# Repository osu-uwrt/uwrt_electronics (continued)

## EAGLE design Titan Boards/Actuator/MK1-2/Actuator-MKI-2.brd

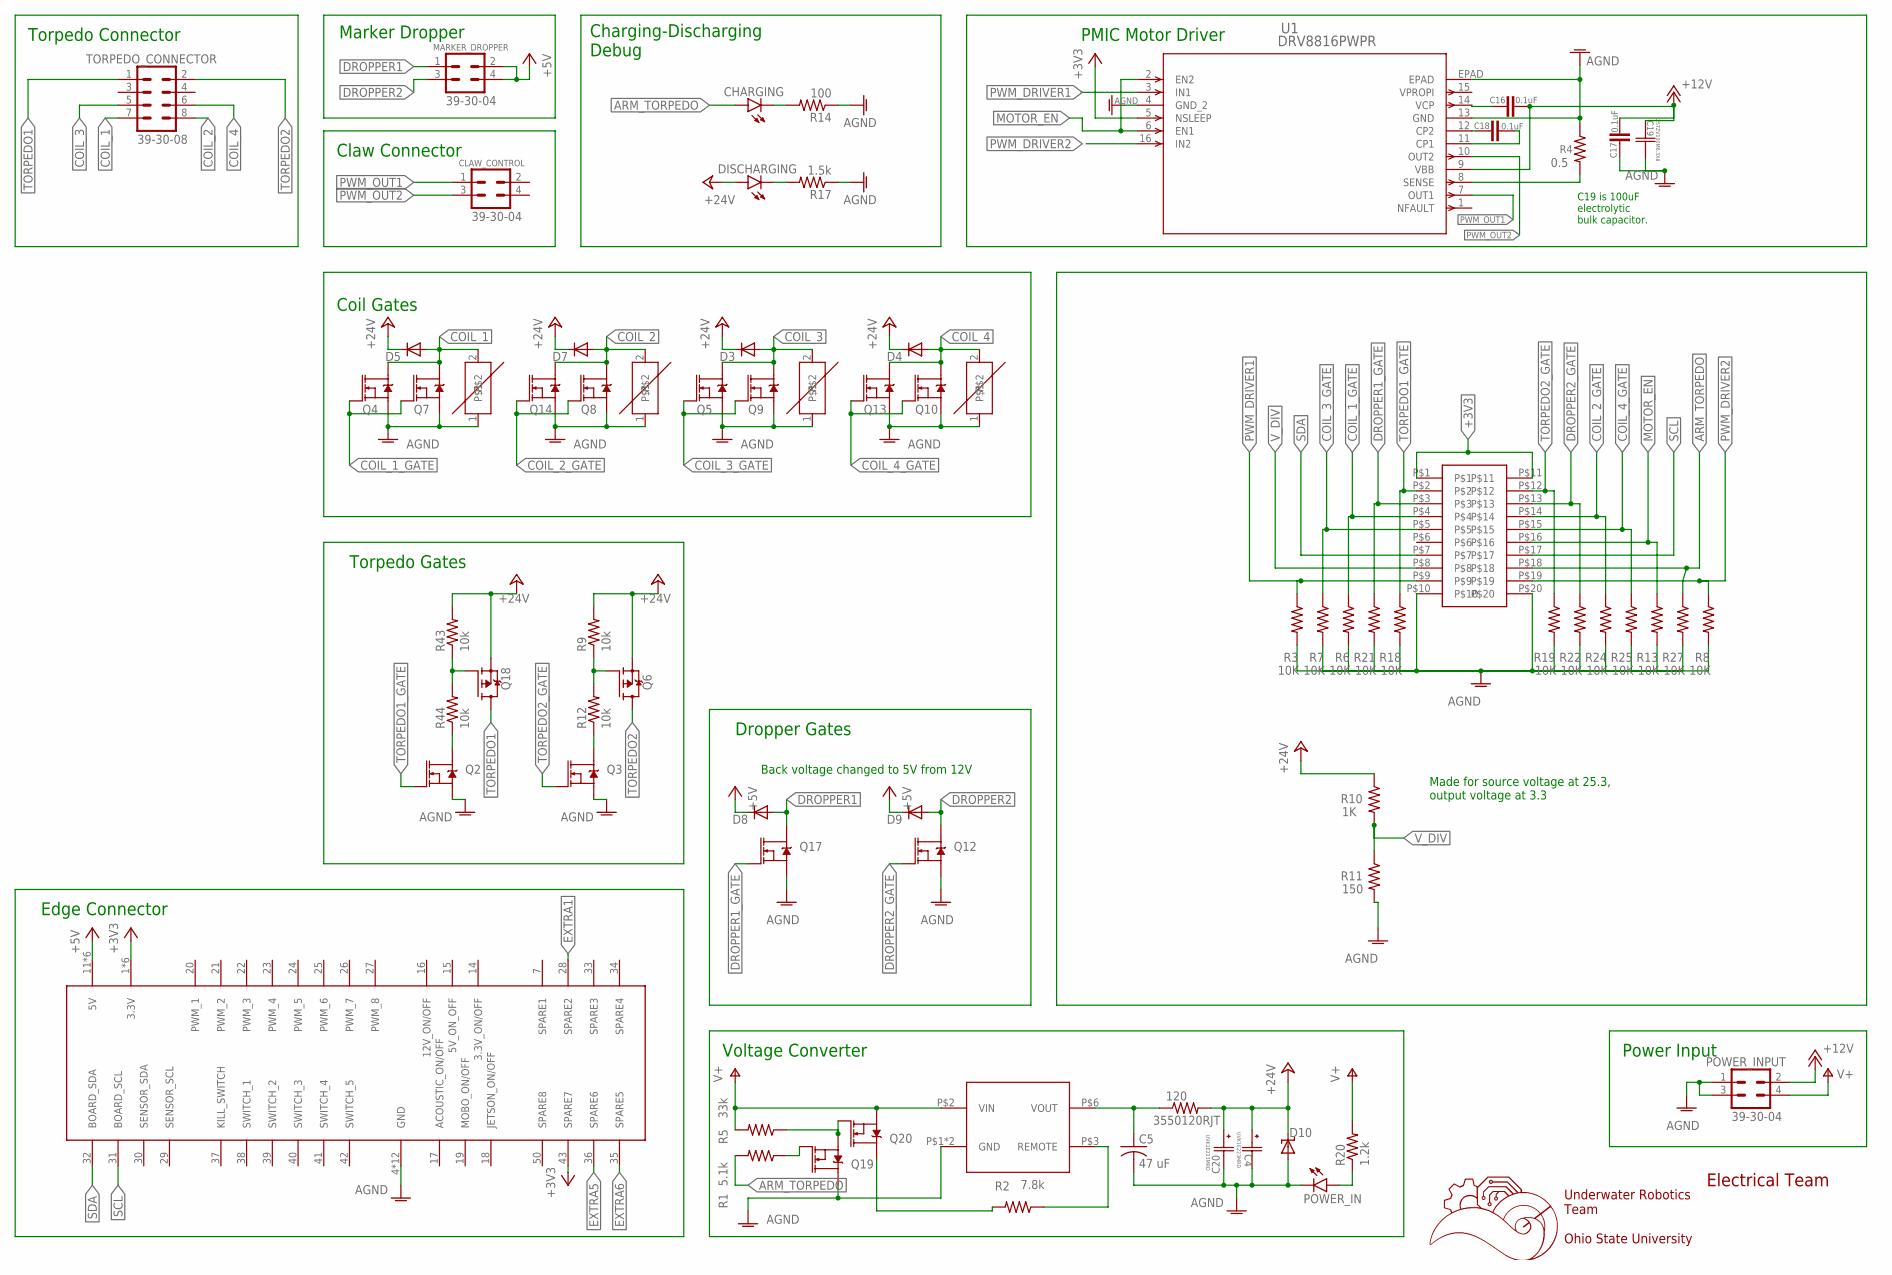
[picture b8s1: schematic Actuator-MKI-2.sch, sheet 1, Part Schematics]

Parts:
120: 3550120RJT
C4, C20: UVK1E223MRD; CAP_UFW_25X50_NCH
C5: 47 uF; C1206K
C16, C17, C18: 0.1uF; C0603
C19: 25TZV100M6.3X8; CAP_J-V_6P3X8_RUB
CHARGING: LEDCHIPLED_0603; CHIPLED_0603
CLAW_CONTROL: 39-30-04; 39-30-?04?
D3, D4, D5, D7, D8, D9: DIODE-SMB; SMB
D10: SUPPRESSOR-SMBJ; SMBJ
DISCHARGING: LEDCHIPLED_0603; CHIPLED_0603
MARKER_DROPPER: 39-30-04; 39-30-?04?
POWER_IN: LEDCHIPLED_0603; CHIPLED_0603
POWER_INPUT: 39-30-04; 39-30-?04?
Q2, Q3, Q4, Q5, Q7, Q8, Q9, Q10, Q12, Q13, Q14, Q17, Q19, Q20: MOSFET-NCH-AO3404A; SOT23-3
Q6, Q18: FDD4141TO252; TO252
R1: 5.1k; R0603
R2: 7.8k; R0603
R3, R6, R7, R8, R13, R18, R19, R21, R22, R24, R25, R27: 10K; R0603
R4: 0.5; R0805
R5: 33k; R0603
R9, R12, R43, R44: 10k; R0603
R10: 1K; R0603
R11: 150; R0603
R14: 100; R0805
R17: 1.5k; R0805
R20: 1.2k; R0805
TORPEDO_CONNECTOR: 39-30-08; 39-30-?08?
U1: DRV8816PWPR; PWP_16
U$1: 5530843-EDGE; 5530843-6-BOARDFINGERS
U$4, U$5, U$7, U$8: ERZ-VF2M270ERZ-VF2M270; RESM8060X320N
U$6: TMR6-2415
U$9: JTAG-SMD

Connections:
+3V3: U1.5 (NSLEEP), U$1.1 (3.3V), U$1.2 (3.3V), U$1.3 (3.3V), U$1.43 (SPARE7), U$1.54 (3.3V), U$1.55 (3.3V), U$1.56 (3.3V), U$9.P$1, U$9.P$11
+5V: D8.C, D9.C, MARKER_DROPPER.2, MARKER_DROPPER.4, U$1.11 (5V), U$1.12 (5V), U$1.13 (5V), U$1.44 (5V), U$1.45 (5V), U$1.46 (5V)
+12V: C16.2, C17.2, C19.1, POWER_INPUT.2, U1.9 (VBB)
+24V: 120.P$2 (2), C4.1, C20.1, D3.C, D4.C, D5.C, D7.C, D10.C, DISCHARGING.A, Q6.2 (S), Q18.2 (S), R9.2, R10.1, R43.2
AGND: C4.2, C5.2, C17.1, C19.2, C20.2, D10.A, POWER_IN.C, POWER_INPUT.1, POWER_INPUT.3, Q2.2 (S), Q3.2 (S), Q4.2 (S), Q5.2 (S), Q7.2 (S), Q8.2 (S), Q9.2 (S), Q10.2 (S), Q12.2 (S), Q13.2 (S), Q14.2 (S), Q17.2 (S), Q19.3 (D), R3.2, R4.1, R6.2, R7.2, R8.2, R11.2, R13.2, R14.1, R17.1, R18.2, R19.2, R21.2, R22.2, R24.2, R25.2, R27.2, U1.4 (GND_2), U1.13 (GND), U1.EPAD, U$1.4 (GND), U$1.5 (GND), U$1.6 (GND), U$1.8 (GND), U$1.9 (GND), U$1.10 (GND), U$1.47 (GND), U$1.48 (GND), U$1.49 (GND), U$1.51 (GND), U$1.52 (GND), U$1.53 (GND), U$4.1, U$5.1, U$6.P$1 (GND), U$6.P$7 (GND), U$7.1, U$8.1, U$9.P$10, U$9.P$20
ARM_TORPEDO: CHARGING.A, R1.2, R27.1, U$9.P$18
COIL_1: D5.A, Q4.3 (D), Q7.3 (D), TORPEDO_CONNECTOR.7, U$8.2
COIL_1_GATE: Q4.1 (G), Q7.1 (G), R6.1, U$9.P$4
COIL_2: D7.A, Q8.3 (D), Q14.3 (D), TORPEDO_CONNECTOR.8, U$7.2
COIL_2_GATE: Q8.1 (G), Q14.1 (G), R24.1, U$9.P$14
COIL_3: D3.A, Q5.3 (D), Q9.3 (D), TORPEDO_CONNECTOR.5, U$5.2
COIL_3_GATE: Q5.1 (G), Q9.1 (G), R7.1, U$9.P$5
COIL_4: D4.A, Q10.3 (D), Q13.3 (D), TORPEDO_CONNECTOR.6, U$4.2
COIL_4_GATE: Q10.1 (G), Q13.1 (G), R25.1, U$9.P$15
DROPPER1: D8.A, MARKER_DROPPER.1, Q17.3 (D)
DROPPER1_GATE: Q17.1 (G), R21.1, U$9.P$3
DROPPER2: D9.A, MARKER_DROPPER.3, Q12.3 (D)
DROPPER2_GATE: Q12.1 (G), R22.1, U$9.P$13
EXTRA1: U$1.28 (SPARE2)
EXTRA5: U$1.36 (SPARE6)
EXTRA6: U$1.35 (SPARE5)
MOTOR_EN: R13.1, U1.2 (EN2), U1.6 (EN1), U$9.P$16
unnamed: C16.1, U1.14 (VCP)
unnamed: R2.1, U$6.P$3 (REMOTE)
unnamed: CHARGING.C, R14.2
unnamed: Q19.1 (G), R1.1
unnamed: Q19.2 (S), Q20.1 (G), R5.1
unnamed: Q20.3 (D), R2.2
unnamed: POWER_IN.A, R20.1
unnamed: DISCHARGING.C, R17.2
unnamed: 120.P$1 (1), C5.1, U$6.P$6 (VOUT)
unnamed: Q18.1 (G), R43.1, R44.2
unnamed: Q2.3 (D), R44.1
unnamed: Q6.1 (G), R9.1, R12.2
unnamed: Q3.3 (D), R12.1
unnamed: R4.2, U1.8 (SENSE)
unnamed: C18.2, U1.11 (CP1)
unnamed: C18.1, U1.12 (CP2)
PWM_DRIVER1: R3.1, U1.3 (IN1), U$9.P$9
PWM_DRIVER2: R8.1, U1.16 (IN2), U$9.P$19
PWM_OUT1: CLAW_CONTROL.1, U1.7 (OUT1)
PWM_OUT2: CLAW_CONTROL.3, U1.10 (OUT2)
SCL: U$1.31 (BOARD_SCL), U$9.P$17
SDA: U$1.32 (BOARD_SDA), U$9.P$7
TORPEDO1: Q18.3 (D), TORPEDO_CONNECTOR.1
TORPEDO1_GATE: Q2.1 (G), R18.1, U$9.P$2
TORPEDO2: Q6.3 (D), TORPEDO_CONNECTOR.2
TORPEDO2_GATE: Q3.1 (G), R19.1, U$9.P$12
V+: POWER_INPUT.4, Q20.2 (S), R5.2, R20.2, U$6.P$2 (VIN)
V_DIV: R10.2, R11.1, U$9.P$8

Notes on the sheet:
Underwater Robotics Team Ohio State University
Electrical Team
Torpedo Connector
Claw Connector
Charging-Discharging Debug
Edge Connector
Voltage Converter
Dropper Gates
Coil Gates
Torpedo Gates
Marker Dropper
Power Input
Back voltage changed to 5V from 12V
PMIC Motor Driver
C19 is 100uF electrolytic bulk capacitor.
Made for source voltage at 25.3, output voltage at 3.3

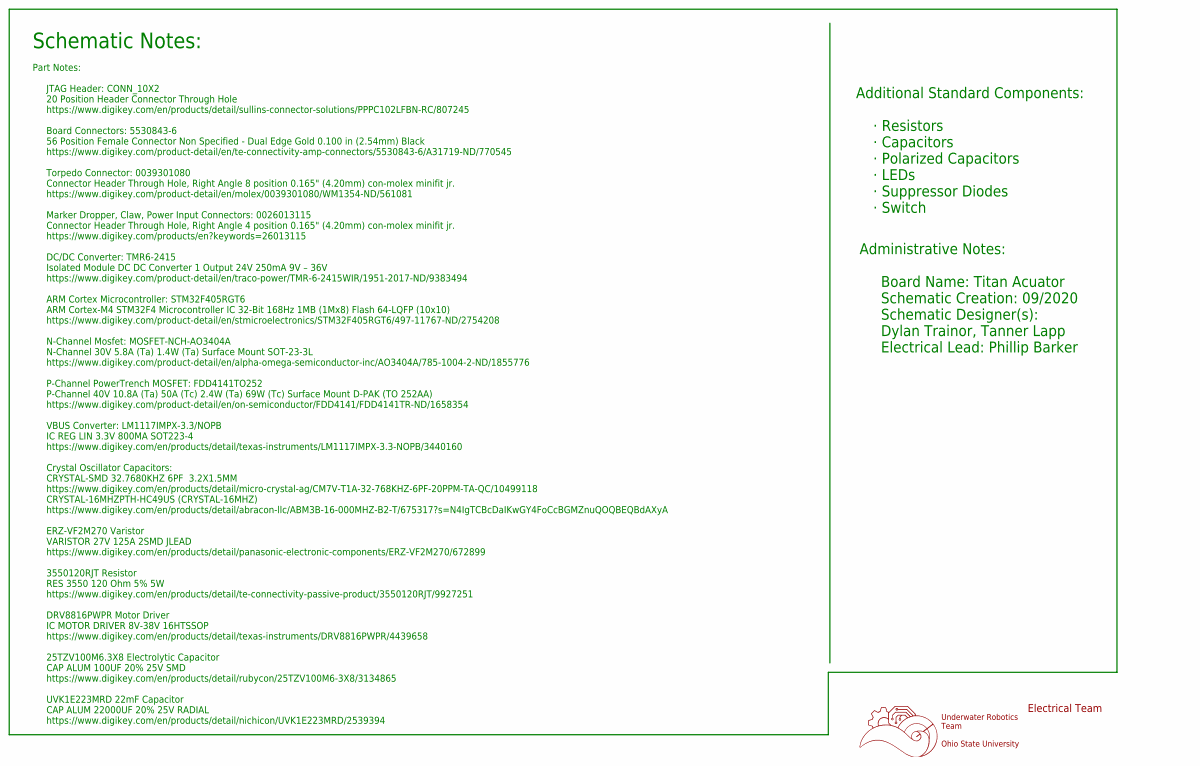
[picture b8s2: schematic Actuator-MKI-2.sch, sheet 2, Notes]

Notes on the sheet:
Underwater Robotics Team Ohio State University
Electrical Team
Schematic Notes:
Part Notes: JTAG Header: CONN_10X2 20 Position Header Connector Through Hole https://www.digikey.com/en/products/detail/sullins-connector-solutions/PPPC102LFBN-RC/807245 Board Connectors: 5530843-6 56 Position Female Connector Non Specified - Dual Edge Gold 0.100 in (2.54mm) Black https://www.digik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
Administrative Notes: Board Name: Titan Acuator Schematic Creation: 09/2020 Schematic Designer(s): Dylan Trainor, Tanner Lapp Electrical Lead: Phillip Barker
Additional Standard Components: · Resistors · Capacitors · Polarized Capacitors · LEDs · Suppressor Diodes · Switch

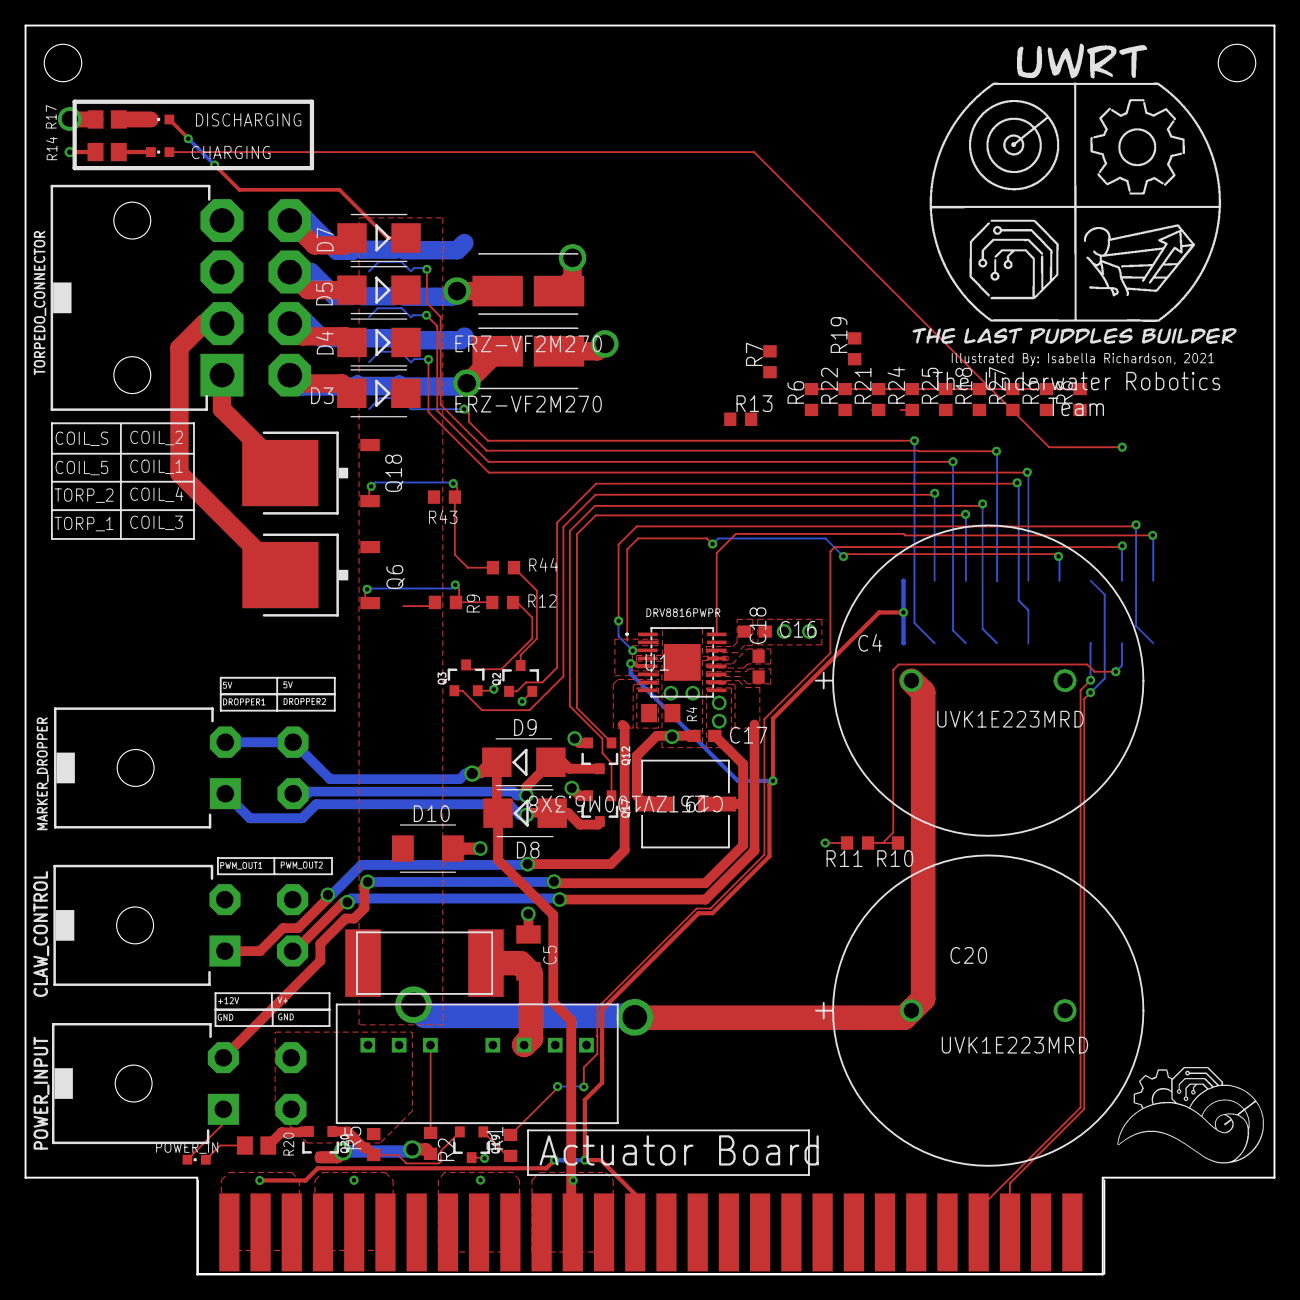
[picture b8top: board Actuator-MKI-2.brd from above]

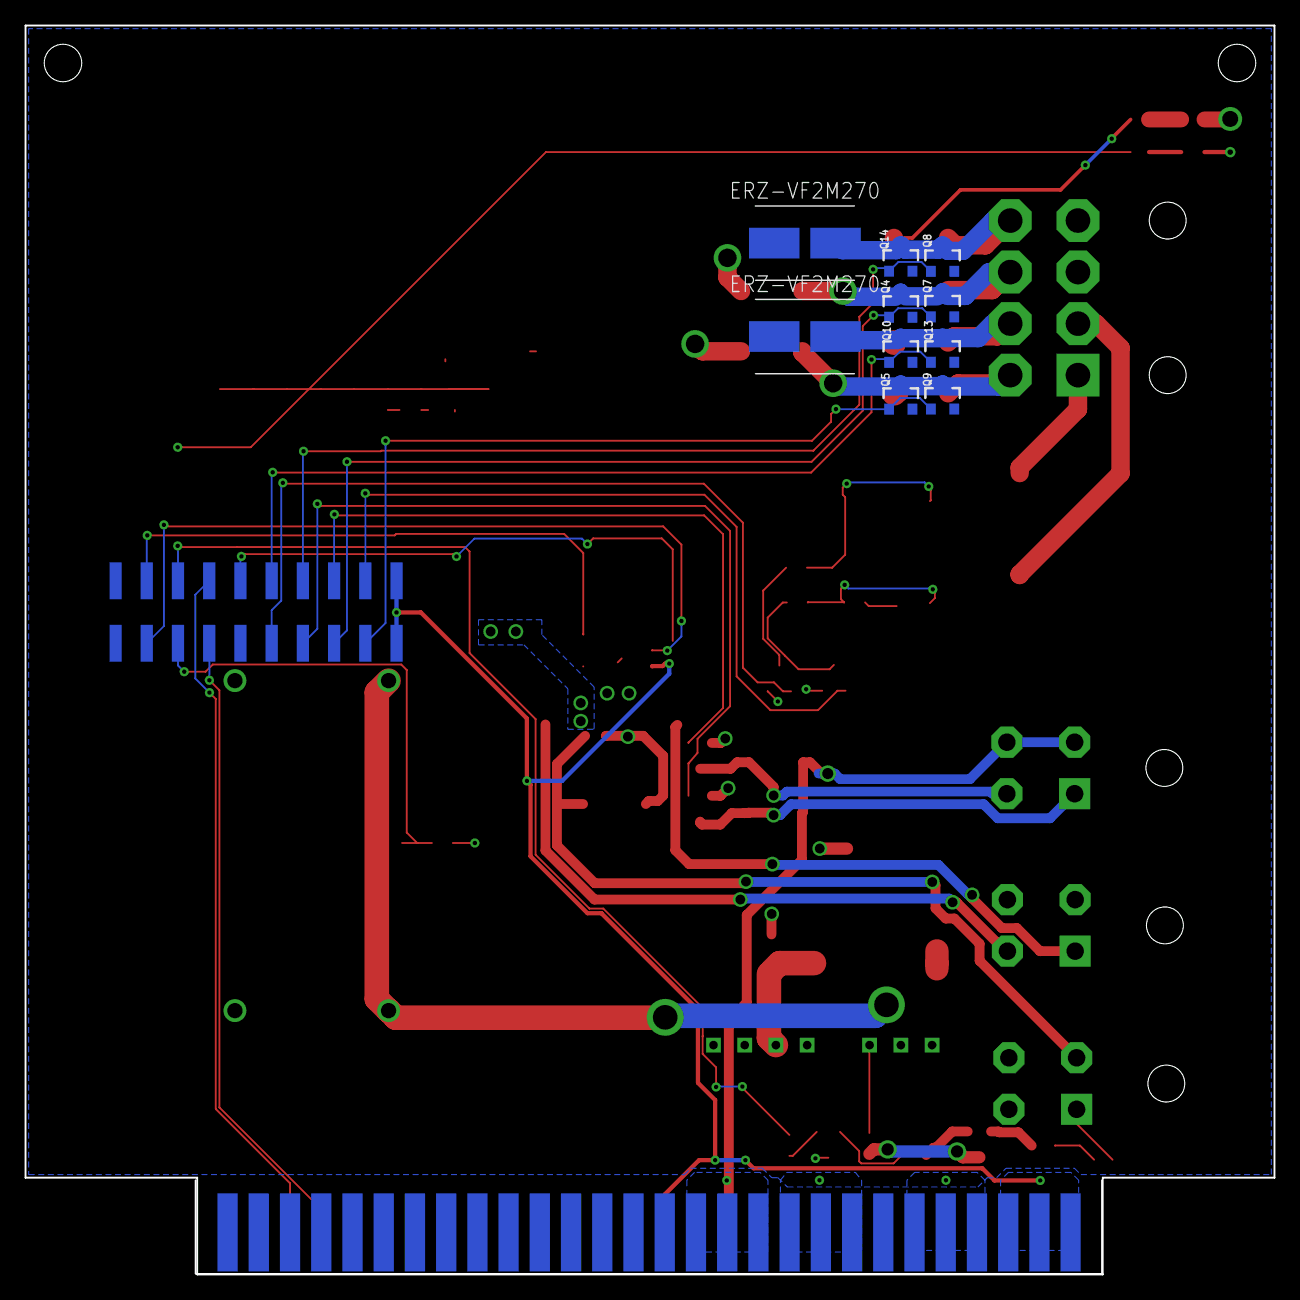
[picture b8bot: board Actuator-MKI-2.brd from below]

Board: 2 copper layers, 101.6 x 101.6 mm, 71 parts (11 on the bottom side), 47 nets.

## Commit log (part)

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2018-10-05 Board template
2018-10-05 Board template (#1)
2018-10-05 Updating board template and acoustics. Started backplane
2018-10-05 deleting unneccesary library
2018-10-05 Updated board template
2018-10-05 Added holes
2018-10-05 Added converter board
2018-10-05 converter work
2018-10-07 Restructure CoPro folders
2018-10-07 Update to use templates
2018-10-07 Updating edge connector
2018-10-07 Copied template to ESC
2018-10-07 added portsto backplane
2018-10-07 Converter board
2018-10-07 Converter board work
2018-10-08 Converter layout finished
2018-10-09 Changing converter board parts
2018-10-09 Created 2-pin screw terminal part
2018-10-09 test
2018-10-14 Modified edge connector to fit current system
2018-10-14 New schematic template and converter fixes
2018-10-14 Touching up acoustics
2018-10-18 Removing errors from board template
2018-10-18 Moved a part for example in ESC
2018-10-18 Converter board first draft
2018-10-19 Fixes to converter
2018-10-21 started battery balancer
2018-10-25 Moved Motor Power up
2018-10-28 added some routing connections
2018-11-01 Almost done with schematic, working on board
2018-11-01 Changed Battery Balancer
2018-11-01 Created 14 pin and 24 in connectors for the ESC board.
2018-11-04 Finished parts for Battery Balancer
2018-11-04 File Directory changed
2018-11-04 Made header part and finished schematic.
2018-11-04 Updated Backplane
2018-11-11 Finished battery balancer. Started routing. git push
2018-11-11 Created new vertical connector, updated 24 pin connector, mostly done with routing.
2018-11-16 Added LEDs onto ESC board
2018-11-16 Backplane Update
2018-11-18 updated battery balancer
2018-12-09 Update copro for f405
2018-12-09 Finished ESC board, need to go back for minor changes.
2019-01-08 adding ethernet to copro schematic
2019-01-08 fixed copro files for f/b annoation
2019-01-13 Rerouted current sensors and added bypass capacitors to ADC
2019-01-15 changed MOSFET
2019-01-19 Updated schematic/board with labels and added capacitor values.
2019-01-20 Took out C9, moved some text
2019-01-20 Finished Backplane
2019-01-22 worked on bard layout
2019-01-27 updating copro board
2019-01-27 fixed the board merge
2019-01-27 continued work on copro schematic
2019-02-03 finished up the initial routing on the copro board layout
2019-02-03 changing planes for ground and power
2019-02-05 finished the copro board layout
2019-02-09 Adding Status Board
2019-02-10 finalized copro
2019-02-10 updated 3v3 voltage controller line
2019-02-10 Adding LEDs
2019-02-10 Update Status Board
2019-02-11 Fixed and updated Battery Balancer
2019-02-12 finished the board layout
2019-02-12 Finishing touches on the ESC board
2019-02-13 Finished status board schematic
2019-02-14 Setting board dimensions and adding back ground plane
2019-02-14 Adding caps and fixing screen
2019-02-17 Finalized the battery balancer
2019-02-18 Updating status schematic
2019-02-19 prettified the board
2019-02-19 Added pull-up resistors to backplane
2019-02-19 Finishing converter and changing parts on BB
2019-02-19 Fixed battery balancer made wires thick and connected everything
2019-02-20 Final changes before order
2019-02-21 Adding links to readme
2019-04-08 add eddy boards
2019-04-08 Started Copro schematic for Eddy
2019-04-08 added power distribution board files
2019-07-13 Converter actuator board
2020-01-12 created fuse library and added fuses to schematic
2020-01-23 Batter Balancer Board Update
2020-01-26 Final BB Board for Review
2020-01-26 Changed Top Connector Position
2020-02-02 Added more LEDs, Shifted part locations and rerouted some lines
2020-02-02 Added fuses to ESC board and reconnected traces.
2020-02-09 Actuator new
2020-02-09 Added connector to BB
2020-02-13 Added via's between BAL_OUT planes
2020-02-23 Added DC_DC converter footprint/library/part
2020-02-27 Finished Actuator
2020-02-27 Power Distribution DC Converter Work
2020-02-28 help
2020-02-28 coprocessor changes
2020-03-01 addded PWM's to connector and adjusted positioning
2020-03-01 added LED
2020-03-01 finished sheet 1, moved items on board around- will add labels to sheet 1 later
2020-03-01 started sheet 2 of schematic, need explanation of esc's the alternating setup is confusing me. Need labels on sheet 1
2020-03-05 Actuator Update
2020-03-05 Eddy PD Work
2020-04-01 I forgot to commit these before for the copro
2020-04-01 temporary
2020-04-02 Finished Schematic needs looked over before starting board
2020-04-20 information about Copro needs
2020-04-26 Power Distribution Changes
2020-04-26 Updated Copro PWM drivers and programming header
2020-04-29 Routing round 2 started-Flip
2020-05-04 further routing done on Copro/backplane
2020-05-11 Eddy backplane *mostly* complete. Just some minor things
2020-05-13 Broken ground plane fixed. Ready for board review
2020-05-13 Power Distribution
2020-05-27 Eddy BB Update
2020-05-28 Added converter library
2020-06-08 Eddy Backplane Ready for board review round 1
2020-06-10 Nearly Done with board just need to expand battery power and 3 volt power planes i think
2020-07-01 Titan Board Template V1
2020-07-06 update with board review changed
2020-07-08 Eddy Power Distribution Review Changes
2020-07-09 Titan folder added
2020-07-09 Puddles board rework: Battery Balancer
2020-07-15 Puddles board rework 2020: Battery Balancer and Actuator
2020-07-24 updated puddles board rework ESC and Copro finished
2020-07-28 Initial schematic design backplane
2020-07-31 First final version of Titan Backplane Schematic
2020-08-05 Schematic template added to template folder
2020-08-17 Titan Backplane Final Version 1
2020-08-26 Backplane connector and spacing revisions
2020-09-10 Getting ready to add new changes with fault lights and fuses. Changed to format for Xavier computer
2020-09-13 Initial Actuator schematic
2020-09-16 Organization of Actuator board schematic
2020-09-17 Changed LED circuits 90% done with schematic
2020-09-18 Actuator organization
2020-09-24 Started parts list of battery balancer
2020-09-24 modified board temporarily
2020-09-24 Actuator sch Notes Page
2020-09-25 Changed capacitors and updated parts list
2020-09-26 ESC schematic and initial board work
2020-09-27 Finished parts list for battery balancer
2020-10-01 Updated Connectors, changed required voltage for PLTA
2020-10-01 Change copro pins
2020-10-01 Added notes to make changes
2020-10-01 testcommit
2020-10-04 Changes resistor model
2020-10-04 switched actuator and copro backplane connectors
2020-10-04 Copro updates
2020-10-06 backplane reorientation changes
2020-10-08 Seperated fan and lighting and added web addresses
2020-10-08 fixed connectors
2020-10-11 changed wiring on fan and lighting and more data sheet links
2020-10-11 Fixed R1, Flipped a connector on the board, and moved components around off the board to easier tell what is connected
2020-10-11 Additional Changes
2020-10-15 Rearranged LED layout
2020-10-15 This is a test commit
2020-10-16 Changed LED layout going to alter for AND and Inverters
2020-10-18 added AND IC to library and schematic
2020-10-18 put led's to and gate, voltage needs stepped up or down
2020-10-18 added connectors
2020-10-19 resistor changes
2020-10-22 Organized Board Some more, redid some pin organization for later
2020-10-22 Uhh added Iverter library and set up leds for pins, still needs step up thing for leds
2020-10-22 worked a bit on board and fixed schematic error on sheet 3
2020-10-23 Added Functional Schematic and updated library and started board
2020-10-23 Stepped up for AND
2020-10-25 Created CoPro Board File
2020-10-25 Add routing for second LED
2020-10-26 cleaned up sheet 6 of pd board
2020-10-27 fixed mismatched inverter inputs and outputs, fixed (?) 5V LED
2020-10-29 put more on board, did draft routing
2020-11-01 Panelized Board
2020-11-01 Fixed Panelization
2020-11-01 Copro Board Work
2020-11-06 tanner first actuator upload
2020-11-06 folder revision
2020-11-06 Board Fully Routed and ready for a good roatsting, have some DRC questions
2020-11-08 ESC work
2020-11-10 Finished Copro V1
2020-11-12 Titan Actuator Revision
2020-11-12 actuator board work TL
2020-11-13 actuator board TL
2020-11-13 Replaced Inverter IC to SMD routes
2020-11-13 Routed new IC
2020-11-15 more esc work
2020-11-15 Schem Updates
2020-11-15 light board review changes
2020-11-16 Made battery balancer schematic look 1000% better
2020-11-20 Start of board review change, Actuator
2020-11-20 Larger Soldering Pads
2020-11-20 Board Review schem changes pt 1.
2020-11-20 Battery balancer major update
2020-11-29 started work on copro modifications
2020-11-29 eNgINeEriNG
2020-11-29 Backplane design review changes
2020-11-29 organization, added stuff to schematic
2020-11-29 continued updating copro
2020-12-04 fixed connectors and routed a little
2020-12-06 Calculated resistor values for fault detector circuit
2020-12-13 Actuator VBUS converter, crystal changes
2020-12-13 continued routing
2020-12-18 updated power distribution parts list
2020-12-18 continued routing and updated parts list
2020-12-20 Actuator trace width, start of changing FETs
2020-12-22 Actuator double MOSFET addition
2021-01-08 more changes to ESC board
2021-01-14 Review Actuator changes, varistors
2021-01-14 Added exclusion to oscillator
2021-01-15 ESC board updates
2021-01-15 changed addresses
2021-01-17 finished DRC
2021-01-17 worked on design report complaints
2021-01-17 FInal ESC after review
    See summary
2021-01-22 Changed connectors, per new list, began rerouting with larger balanced plane
2021-01-24 Added My President Design to Board
2021-01-24 adjusted connectors, routed more
2021-01-26 CoPro - Increased some trace widths | Opened up ground plane | added decoupling capacitors to Main MicroController
2021-01-31 VBUS addition
2021-01-31 Increased some trace widths
2021-01-31 Killswitch and Switch1 connections
2021-01-31 Library added for 8 pin molex
2021-02-04 Acoustics connector on titan backplane
2021-02-04 finished routing again, pending final review, need to fill out order forms and edit text for clear instillation
2021-02-05 Actuator order sheet
2021-02-06 updating actuator board order sheet
2021-02-07 updates, cleaned labels
2021-02-07 Backplane and Actuator order sheets
2021-02-12 Routed kill and aux switches
2021-02-12 updated library for camera cage breakout
2021-02-12 updated library for cage breakout
2021-02-14 schematic work for camera cage breakout
2021-02-24 modified a lot of finalizing things, generated CAM data
2021-02-26 Backplane switch connector spare 2 to switch 1
2021-02-26 Backplane board decals
2021-03-01 final commit for ESC board, resistor values changed across boards for order ease
2021-03-02 Changing puddles values
2021-03-02 Removing # files
2021-03-02 updates to puddles board rework actuator and BB.
2021-03-05 Changing puddles actuator crystal caps
2021-03-07 Titan Actuator 5W resistor change and library
2021-03-08 Changed name of a MOSFET to line up with ordered part
2021-03-10 Titan Actuator motor driver prep
2021-03-21 final camera cage breakout with gerbers
2021-03-25 Actuator ordersheet updates
2021-03-28 Titan actuator, added 22mF caps
2021-03-28 Perferated external lighting board and removed top right set of vias
2021-04-18 Quick Actuator board revisions
2021-07-25 schematic PDF's added
2021-10-05 Dylans MKI Actuator Revision
2021-10-05 I am pushing schematic and board files mk1 revisions vk.
2021-10-05 added actuator scratch board
2021-10-07 Corrected some wiring and moved name tags
2021-10-07 Deleted Useless Scratch Boards
2021-10-07 Changed via location
2021-10-13 start to actuator design review changes
2021-10-13 Update Actuator-MKI-Revision-DT.brd
    changed design rules
2021-10-13 Updated wire routings to meet design rule requirements
2021-10-20 Actuator work
2021-10-24 Actuator board review final revisions
2021-10-26 Actuator MKI revision order version
2022-03-11 Actuator MKI-2 Revised
2022-03-22 Tempest Actuator MK1-2 Updates
2022-03-24 Actuator MK1-2 Updates
2022-04-14 Actuator MK1-3 updates
2022-04-21 Actuator MKIII updates'
2022-04-28 Actuator MK3 for Review
2022-05-01 Tempest Actuator Updates
